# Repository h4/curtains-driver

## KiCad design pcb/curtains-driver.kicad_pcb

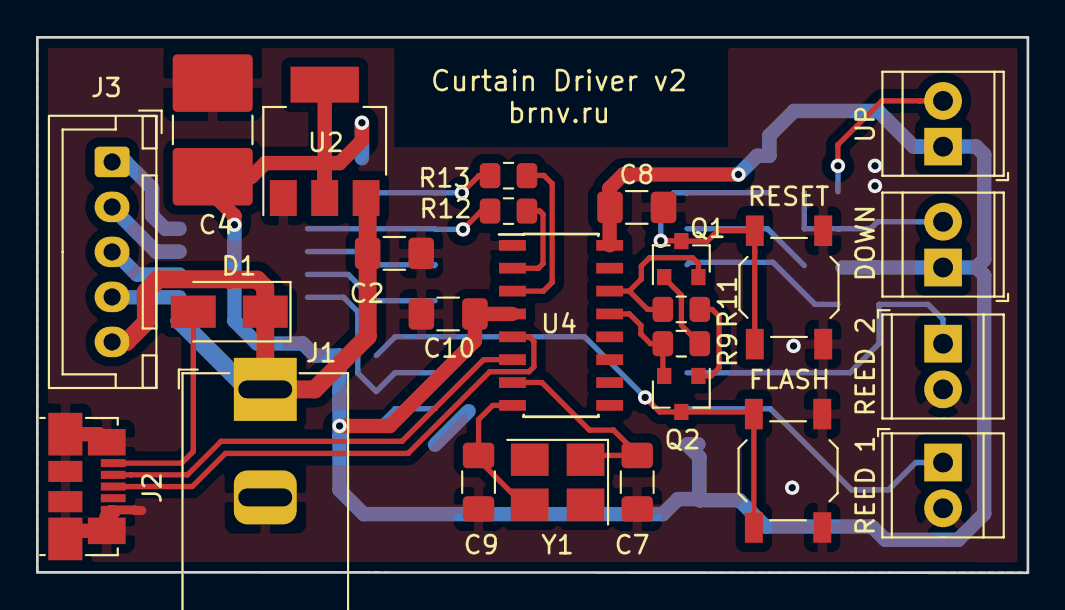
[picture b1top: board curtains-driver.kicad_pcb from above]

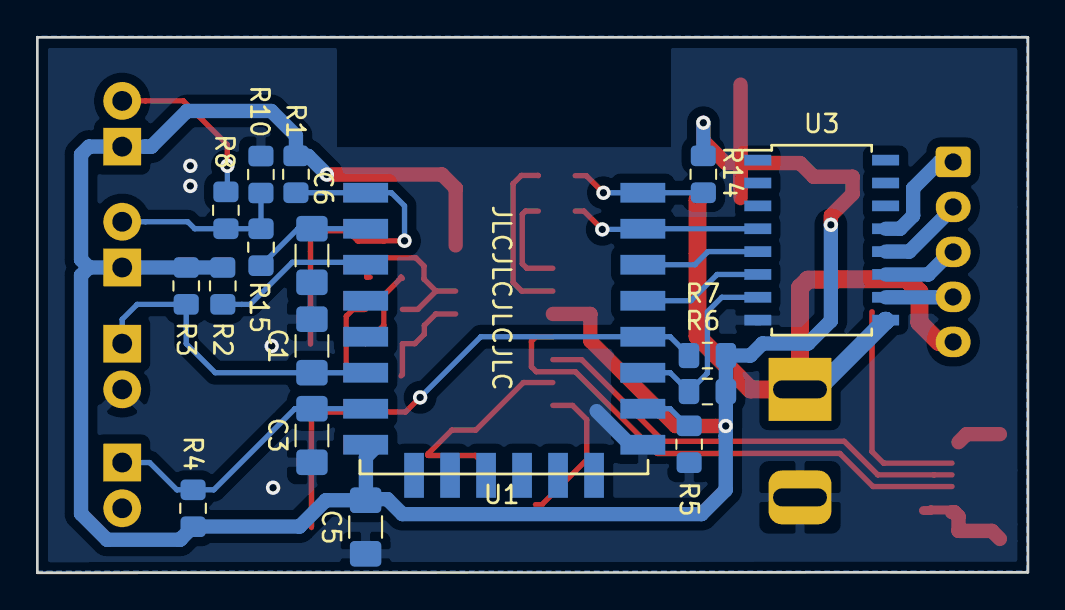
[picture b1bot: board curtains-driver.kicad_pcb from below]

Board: 2 copper layers, 55.0 x 29.7 mm, 42 parts (17 on the bottom side), 32 nets.

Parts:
C1, C3, C5: 0.1uF; C_1206_3216Metric_Pad1.42x1.75mm_HandSolder
C2, C8, C10: 10uF; C_1206_3216Metric_Pad1.42x1.75mm_HandSolder
C4: 100uF; C_2816_7142Metric_Pad3.20x4.45mm_HandSolder
C6: 10nF; C_1206_3216Metric_Pad1.42x1.75mm_HandSolder
C7, C9: 22pF; C_1206_3216Metric_Pad1.42x1.75mm_HandSolder
D1: M7; D_SMA
FLASH: FLASH; SW_SPST_TL3342
J1: Barrel_Jack; BarrelJack_Horizontal_DS_201
J2: USB_B_Micro; USB_Micro-B_Molex_47346-0001
J3: Motor; JST_XH_B05B-XH-A_1x05_P2.50mm_Vertical
J6, J7: Reed_1; TerminalBlock_TE_282834-2_1x02_P2.54mm_Horizontal
Q1, Q2: S8050; SOT-23
R1, R2, R3, R4, R5, R6, R7, R8, R9, R11, R14: 10K; R_0805_2012Metric_Pad1.15x1.40mm_HandSolder
R10: 2K2; R_0805_2012Metric_Pad1.15x1.40mm_HandSolder
R12, R13: 470; R_0805_2012Metric_Pad1.15x1.40mm_HandSolder
R15: 1K; R_0805_2012Metric_Pad1.15x1.40mm_HandSolder
RESET: RESET; SW_SPST_TL3342
SW3: UP; TerminalBlock_TE_282834-2_1x02_P2.54mm_Horizontal
SW4: DOWN; TerminalBlock_TE_282834-2_1x02_P2.54mm_Horizontal
U1: ESP-12F; ESP-12E_SMD
U2: LM1117-3.3; SOT-223-3_TabPin2
U3: ULN2003A; SOIC-16W_5.3x10.2mm_P1.27mm
U4: CH340G; SOIC-16_3.9x9.9mm_P1.27mm
Y1: HC-49; Crystal_SMD_SeikoEpson_FA238V-4Pin_3.2x2.5mm_HandSoldering

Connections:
+5V: C2.1, D1.1, J1.1, J3.5, U2.3, U3.9
/D+: J2.3, U4.5
/D-: J2.2, U4.6
ADC: C6.1, R15.2, U1.2
Earth: C1.2, C2.2, C3.2, C4.2, C5.2, C6.2, C7.2, C8.2, C9.2, C10.2, FLASH.2, J1.2, J2.5, J2.6, J6.2, J7.2, R5.1, R10.1, RESET.1, U1.9, U2.1, U3.8, U4.1
GPIO0: FLASH.1, Q2.3, R7.2, U1.12
unnamed: C1.1, J6.1, R3.1, U1.6
unnamed: C3.1, J7.1, R4.1, U1.7
unnamed: C7.1, U4.7, Y1.1
unnamed: C9.1, U4.8, Y1.3
unnamed: D1.2, J2.1
unnamed: J3.1, U3.13
unnamed: J3.2, U3.12
unnamed: J3.3, U3.11
unnamed: J3.4, U3.10
unnamed: Q1.1, R9.1
unnamed: Q1.2, R11.2, U4.14
unnamed: Q2.1, R11.1
unnamed: Q2.2, R9.2, U4.13
unnamed: R2.1, U1.3
unnamed: R5.2, U1.10
unnamed: R6.2, U1.11, U3.7
unnamed: R8.2, SW4.2
unnamed: R8.1, R10.2, R15.1, SW3.2
unnamed: R12.2, U4.2
unnamed: R13.2, U4.3
unnamed: U1.13, U3.6
unnamed: U1.14, U3.5
RST: Q1.3, R1.1, RESET.2, U1.1
RXD: R12.1, U1.15, U3.4
TXD: R13.1, R14.1, U1.16
VCC: C4.1, C5.1, C8.1, C10.1, R1.2, R2.2, R3.2, R4.2, R6.1, R7.1, R14.2, SW3.1, SW4.1, U1.8, U2.2, U4.4, U4.16

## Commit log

2018-12-23 Refactor Circuit
2019-01-02 Add USB-UART chip
2019-01-08 Code sample
2019-01-13 Add Datasheets
2019-01-13 Switch to AccellStepper library
2019-01-14 Add notes
2019-04-07 Update PCB
2019-04-07 Scaffold firmware
2019-05-22 Fix stepper initialization
2019-05-22 Store reed pins to var
2019-06-11 Minimal working result
2019-07-03 Simplify buttons processing
2019-07-08 Fix kernel fault
2019-07-08 Change PWM and UART circuit
2019-07-10 Update gitignore
2019-07-10 Change ADC resistor divider nominals
2019-07-10 Read UP/DOWN buttons correctly
2019-07-10 Make terminals labels visible after wirig
2019-07-14 Read buttons values in timer intrerupt callback
2019-07-28 Process long pressed button
2019-09-28 Add controlling via MQTT
2019-09-29 Add Cap drawing
2019-10-01 Run motor continiusly
2019-11-10 Setup OTA
2019-12-22 Process reed signals regard to drive direction
2019-12-29 Add edge state checking
2020-01-06 Refactor int types and roll direction
2020-01-12 Add new Blind Mount
2020-01-12 Rename mount files
